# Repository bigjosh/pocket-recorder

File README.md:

# Pocket Recorder Hardware Workspace

Ready-to-iterate KiCad 8/9 hardware workspace for the **Low-Power Outdoor Audio Recorder** (`30.0 x 48.0 mm`, 4-layer 1.6 mm PCBWay Matte-Black ENIG, STM32U595RJT6Q / U5A5 drop-in, TDK T5837 PDM mic, RV-3032-C7 RTC, Hirose DM3D-SF microSD).

## Contents
- `SPEC.md` — Original hardware specification.
- `GEMINI.md` — Persistent agent context (all 13 locked design decisions, hard mechanical constraints, STM32U5 pin-swap guardrails, and Definition of Done) loaded automatically by **Gemini CLI**.
- `build_pocket_recorder.py` — Generates `pocket_recorder_hw/pocket_recorder.kicad_pro`, `pocket_recorder.kicad_pcb`, `pocket_recorder_bom.csv`, and `export_pcbway_gerbers.sh`.
- `build_pocket_recorder_sch.py` — Generates the 1:1 synchronized `pocket_recorder_hw/pocket_recorder.kicad_sch`.
- `verify.py` — Automated gatekeeper script (mechanical assertions, sch<->pcb parity, Freerouting CLI bridge, KiCad ERC/DRC JSON parser, and layer SVG/PNG renders).
- `pocket_recorder_hw/` — Pre-generated KiCad 8/9 project, BOM, and PCBWay Gerber export script.
- `.gemini/settings.json.example` — Optional template for adding `KiCAD-MCP-Server` to Gemini CLI.

## Quick Start with Gemini CLI

1. **Initialize Git** so the agent can checkpoint and revert placement/routing trials safely:
   ```bash
   git init
   git add .
   git commit -m "Initial verified architecture, schematic, and pre-placed 4L PCB"
   ```

2. **Check local tools:**
   ```bash
   kicad-cli --version
   python3 verify.py --mech-only
   ```
   *(Install [Freerouting](https://github.com/freerouting/freerouting/releases) to enable automated routing via `python3 verify.py --route`.)*

3. **Launch Gemini CLI** in this directory:
   ```bash
   gemini
   ```
   Confirm `GEMINI.md` and `SPEC.md` loaded with `/memory show`, then prompt:
   > Review `GEMINI.md` and run `python3 verify.py`. Iteratively refine component placement, safe STM32 pin swaps, critical-net routing (`USB_DP`/`DM` 90R, `L1`/`L2` switch loops, `Y1` HSE, `MK1` PDM), and Freerouting passes until `verify.py` exits 0 with 0 ERC, 0 DRC, and 0 unrouted nets, then export `pocket_recorder_pcbway_gerbers.zip`.

## PCBWay Order Settings (Ready to Fab)
- **Upload Archive:** `pocket_recorder_hw/pocket_recorder_pcbway_gerbers.zip` (full turnkey bundle with BOM, CPL, KiCad sources & 3D renders: `pocket_recorder_hw/pocket_recorder_production_package_v1.0.0.zip`)
- **Size:** `30.0 x 48.0 mm`, `R1.5 mm` corners
- **Layers / Thickness:** 4 Layers, `1.6 mm`, FR-4 TG150-160 (`1 oz` outer / `0.5 oz` inner)
- **Finish:** ENIG (1U" or 2U")
- **Solder Mask:** **Matte Black** (PCBWay Special Options)
- **Silkscreen:** White — **Both Sides** (`F.SilkS` carries minimalist flanking upward arrows, hole rings, and unlock/lock icons; `B.SilkS` carries parts-side legends)
- **Via Process:** Tenting vias (all vias covered by solder mask)
- **Impedance Control:** `90 ohm +/-10%` differential pair (`USB_DP`/`USB_DM`, `19.586 mm`, `0.001 mm` skew, over solid `In1.Cu` GND)
- **Fab Note:** *"Top (`F.Mask`) contains intentional thumbprint graphic openings over copper pour; `F.SilkS` contains intentional white icon artwork. Do NOT add PCBWay order number on Top side—place on Bottom (`B.SilkS`) inside 1.0 mm rim."*

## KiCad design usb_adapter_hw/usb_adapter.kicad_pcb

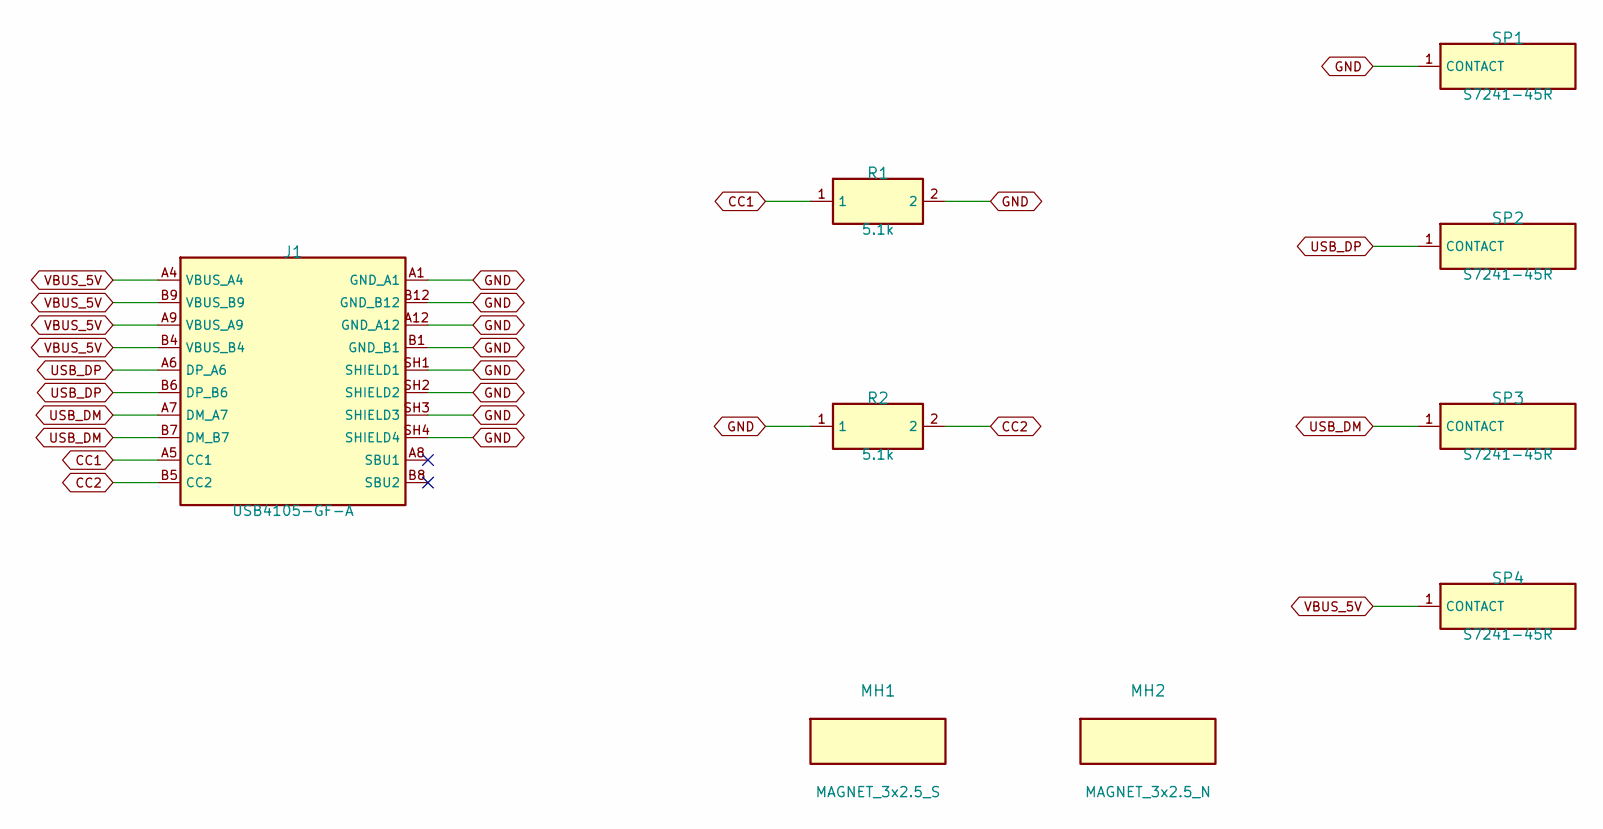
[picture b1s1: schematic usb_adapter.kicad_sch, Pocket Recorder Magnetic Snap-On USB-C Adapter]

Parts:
J1: USB4105-GF-A; USB_C_Receptacle_GCT_USB4105-xx-A_16P_TopMnt_Horizontal; MPN USB4105-GF-A
MH1: MAGNET_3x2.5_S; MagnetHole_3.15mm_NPTH; MPN MAGNET_3x2.5MM_N52
MH2: MAGNET_3x2.5_N; MagnetHole_3.15mm_NPTH; MPN MAGNET_3x2.5MM_N52
R1, R2: 5.1k; R_0603_1608Metric; MPN RC0603FR-075K1L
SP1, SP2, SP3, SP4: S7241-45R; Harwin_S7241-45R_SpringFinger; MPN S7241-45R

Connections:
CC1: J1.A5 (CC1), R1.1
CC2: J1.B5 (CC2), R2.2
GND: J1.A1 (GND_A1), J1.A12 (GND_A12), J1.B1 (GND_B1), J1.B12 (GND_B12), J1.SH1 (SHIELD1), J1.SH2 (SHIELD2), J1.SH3 (SHIELD3), J1.SH4 (SHIELD4), R1.2, R2.1, SP1.1
USB_DM: J1.A7 (DM_A7), J1.B7 (DM_B7), SP3.1
USB_DP: J1.A6 (DP_A6), J1.B6 (DP_B6), SP2.1
VBUS_5V: J1.A4 (VBUS_A4), J1.A9 (VBUS_A9), J1.B4 (VBUS_B4), J1.B9 (VBUS_B9), SP4.1

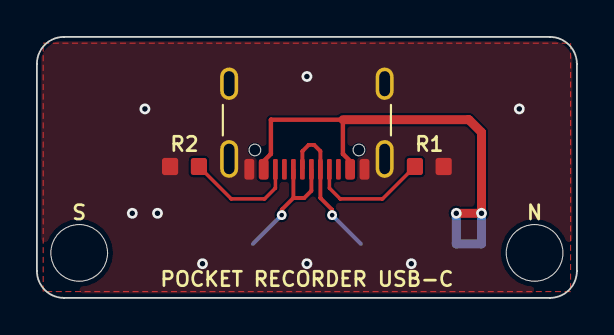
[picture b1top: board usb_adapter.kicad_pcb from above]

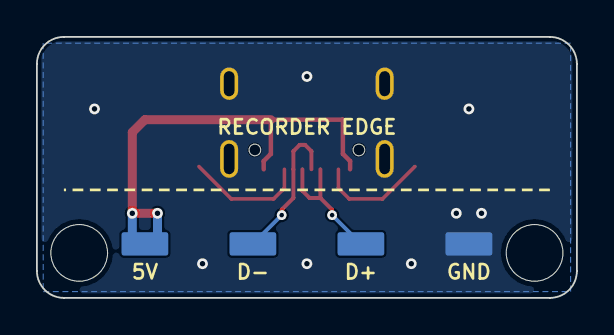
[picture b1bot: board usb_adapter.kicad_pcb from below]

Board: 2 copper layers, 30.0 x 14.5 mm, 9 parts (4 on the bottom side), 6 nets.

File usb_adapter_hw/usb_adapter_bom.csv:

Designator,Qty,MPN,Manufacturer,Package,Description,Order_Link
J1,1,USB4105-GF-A,GCT,USB-C 16P Top-Mount,USB 2.0 Type-C Receptacle (4x THT Shield Legs),https://www.digikey.com/en/products/detail/gct/USB4105-GF-A/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
"R1,R2",2,RC0603FR-075K1L,Yageo,0603,5.1k 1% USB-C UFP CC1/CC2 Pull-Down,https://www.digikey.com/en/products/detail/yageo/RC0603FR-07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
SP1-SP4,4,S7241-45R,Harwin,SMT 3.0x1.5x1.3mm,"Gold SMT Spring Finger (1.0mm working H, ~40gf)",https://www.digikey.com/en/products/detail/harwin-inc/S7241-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

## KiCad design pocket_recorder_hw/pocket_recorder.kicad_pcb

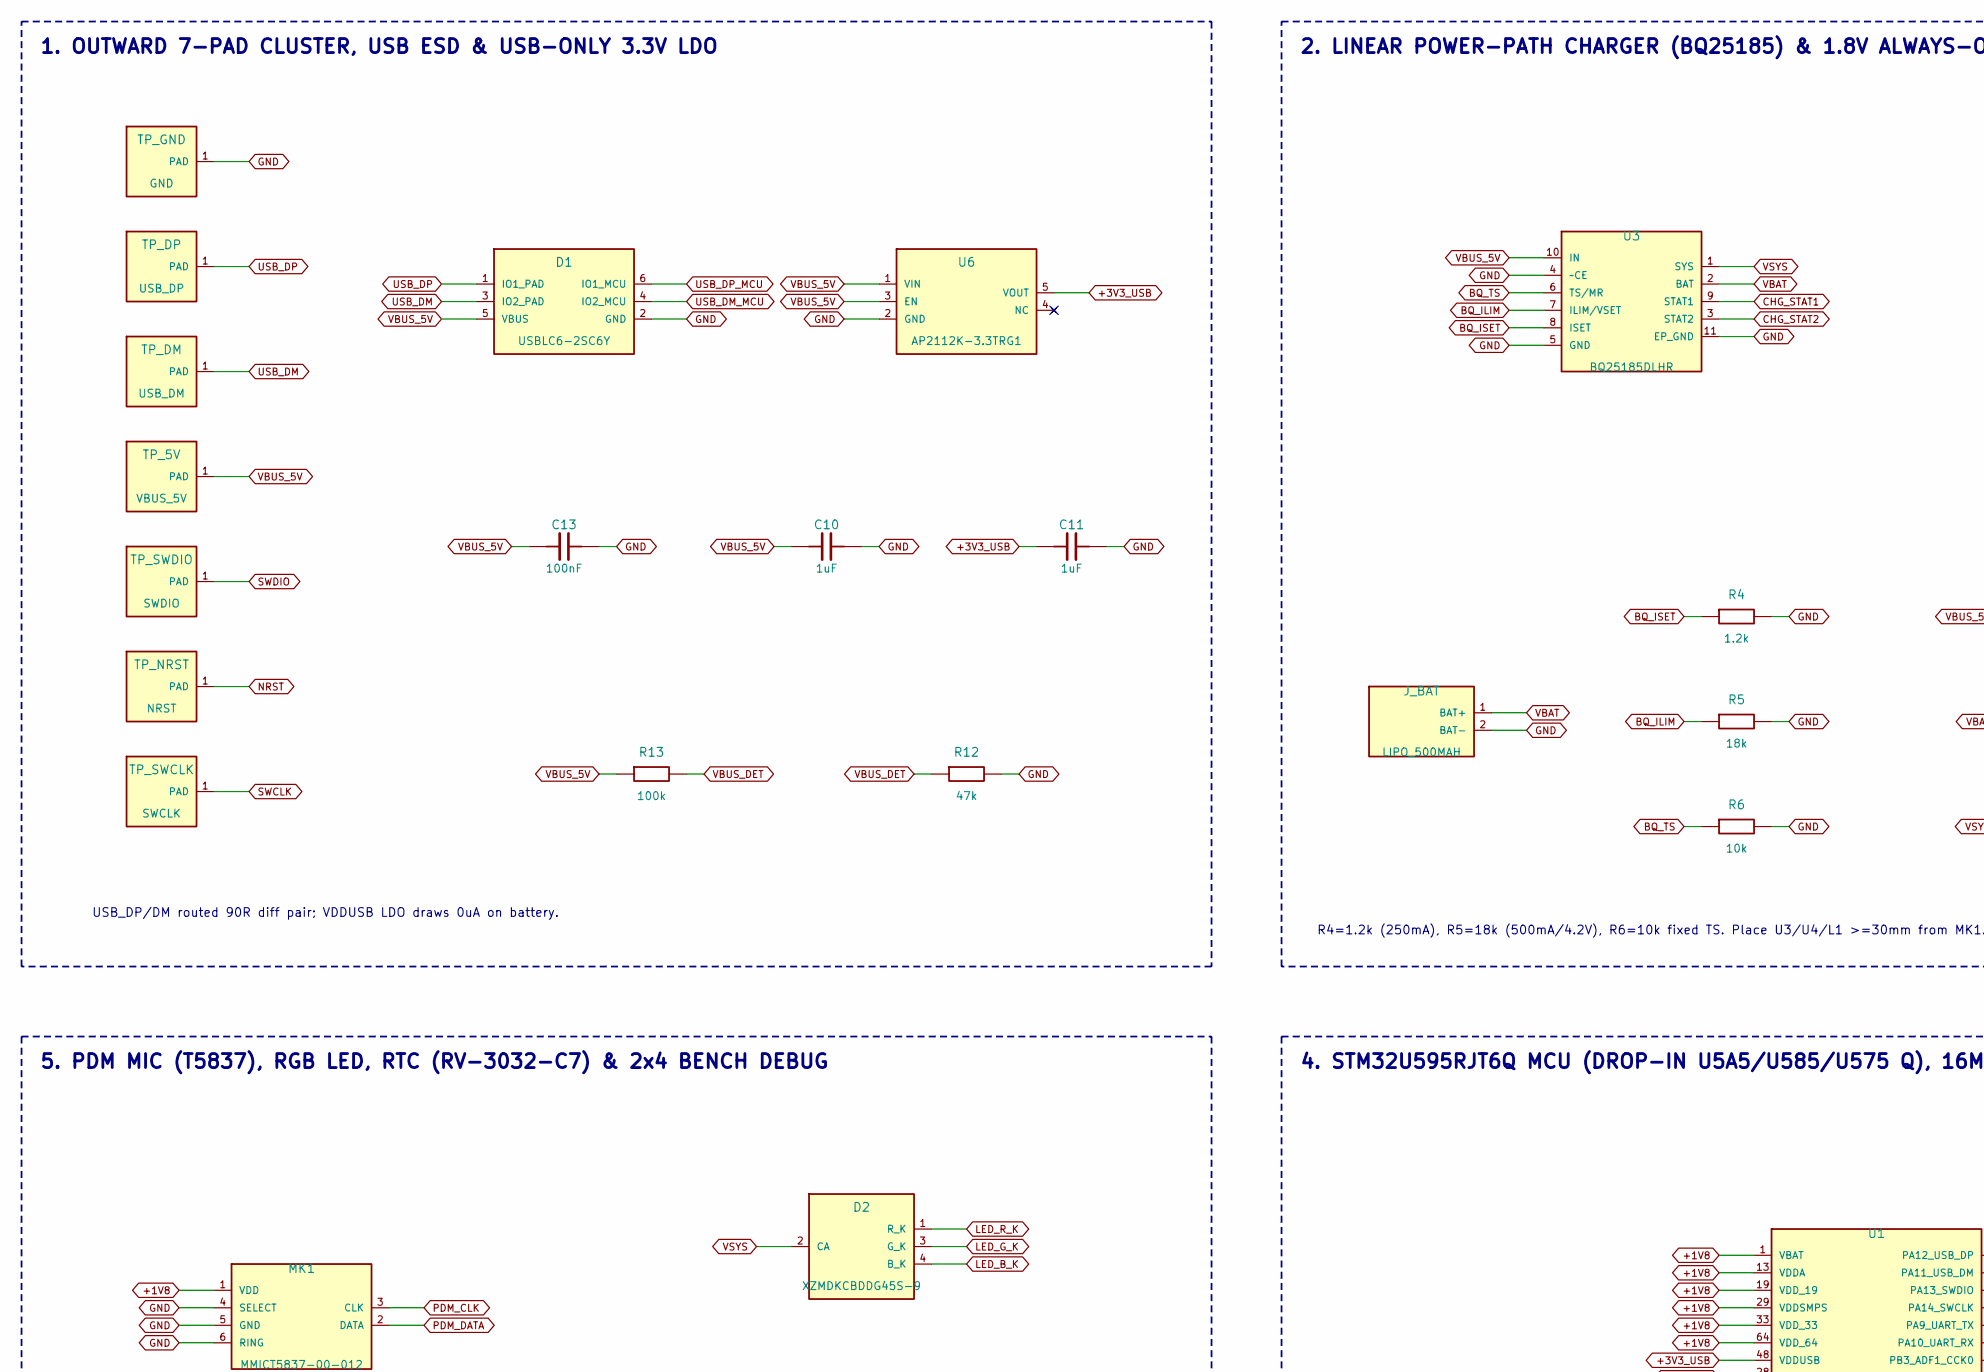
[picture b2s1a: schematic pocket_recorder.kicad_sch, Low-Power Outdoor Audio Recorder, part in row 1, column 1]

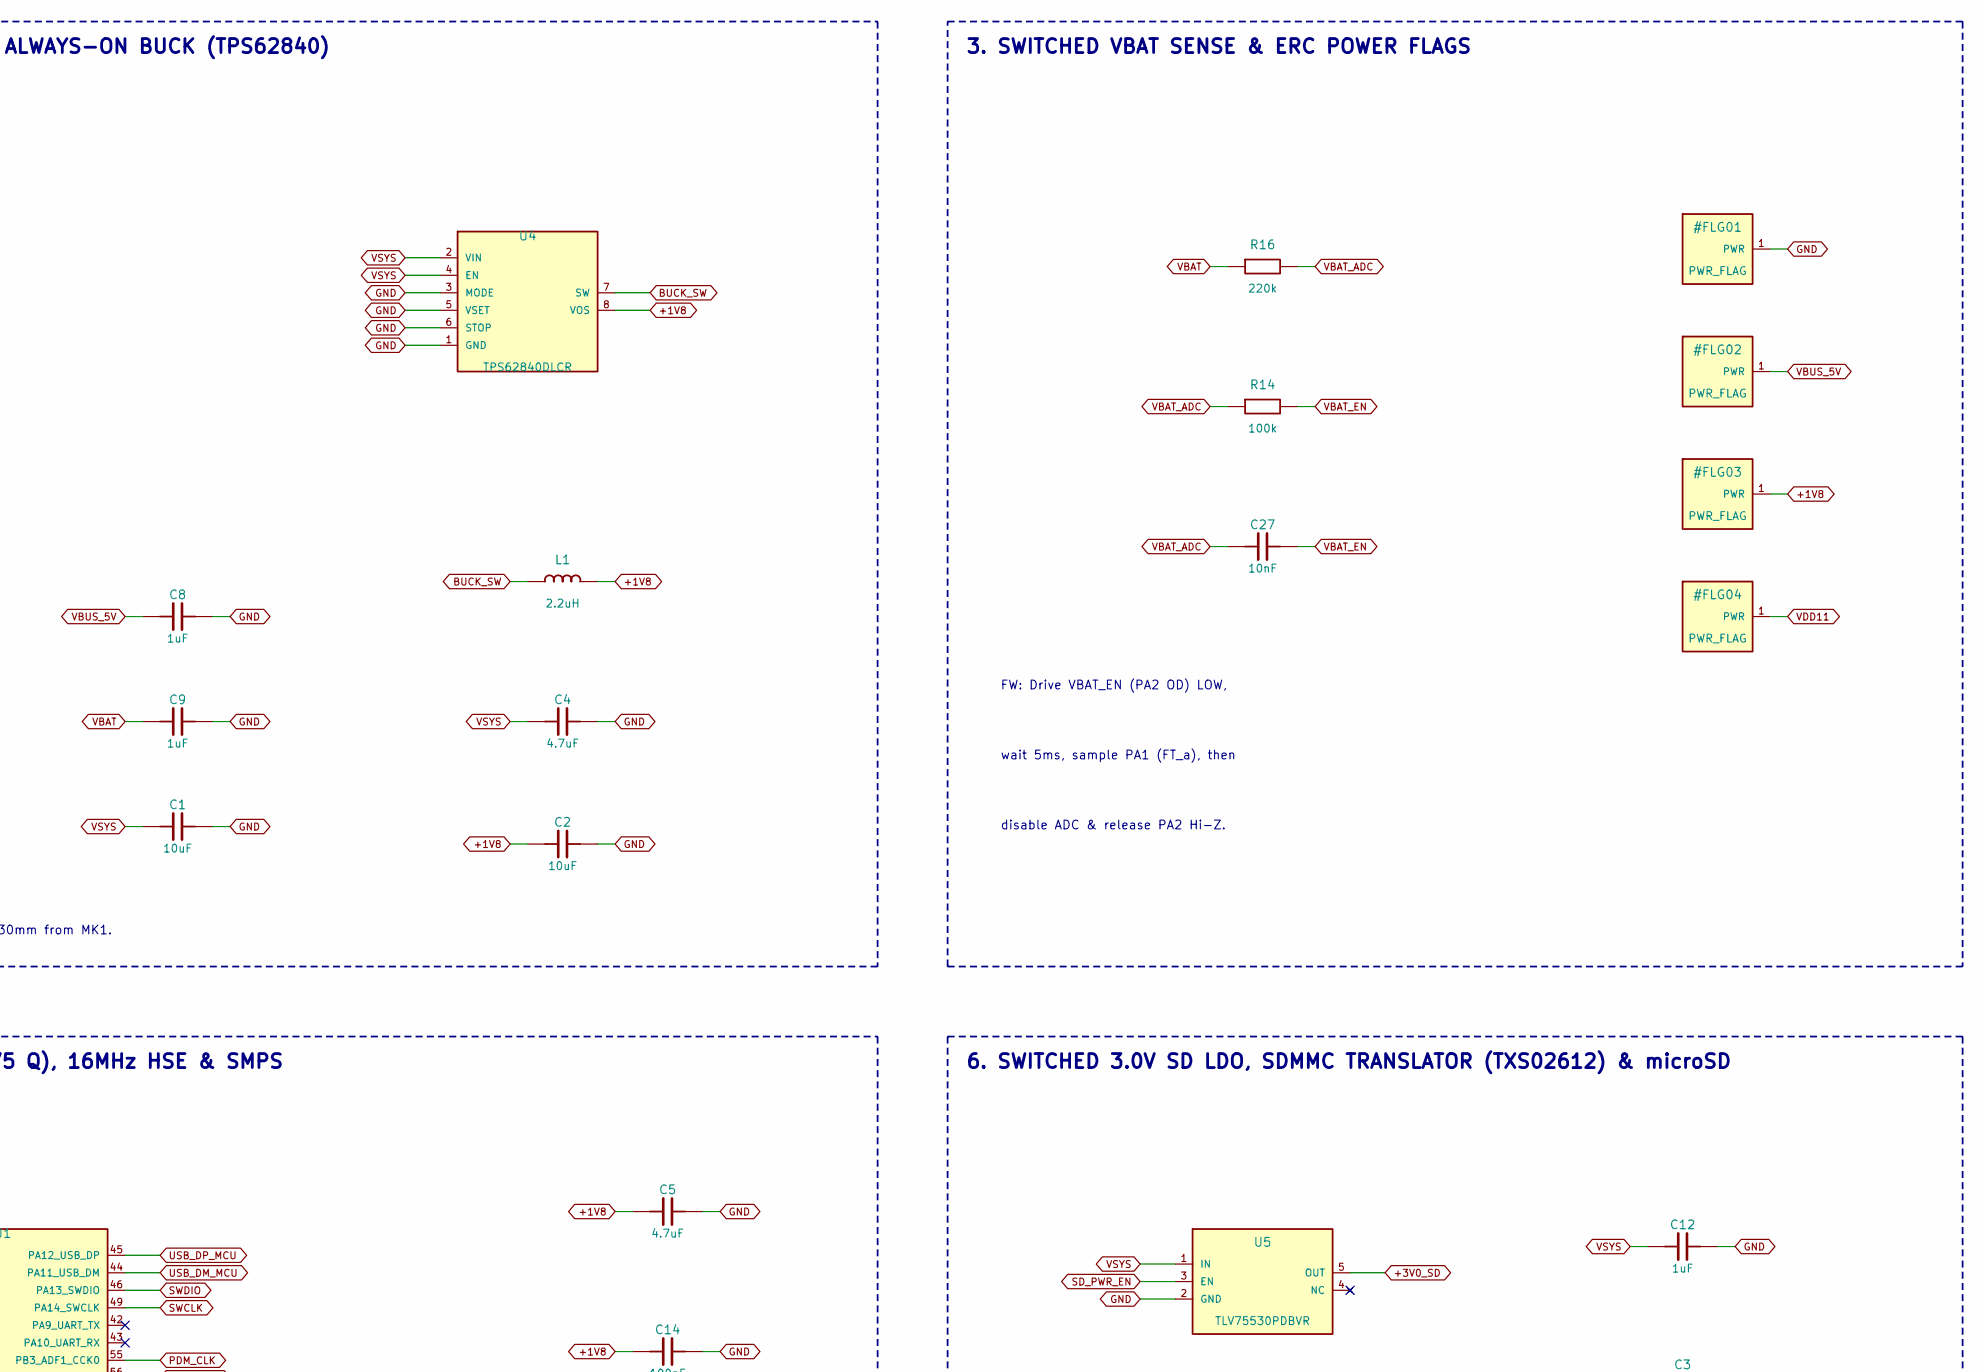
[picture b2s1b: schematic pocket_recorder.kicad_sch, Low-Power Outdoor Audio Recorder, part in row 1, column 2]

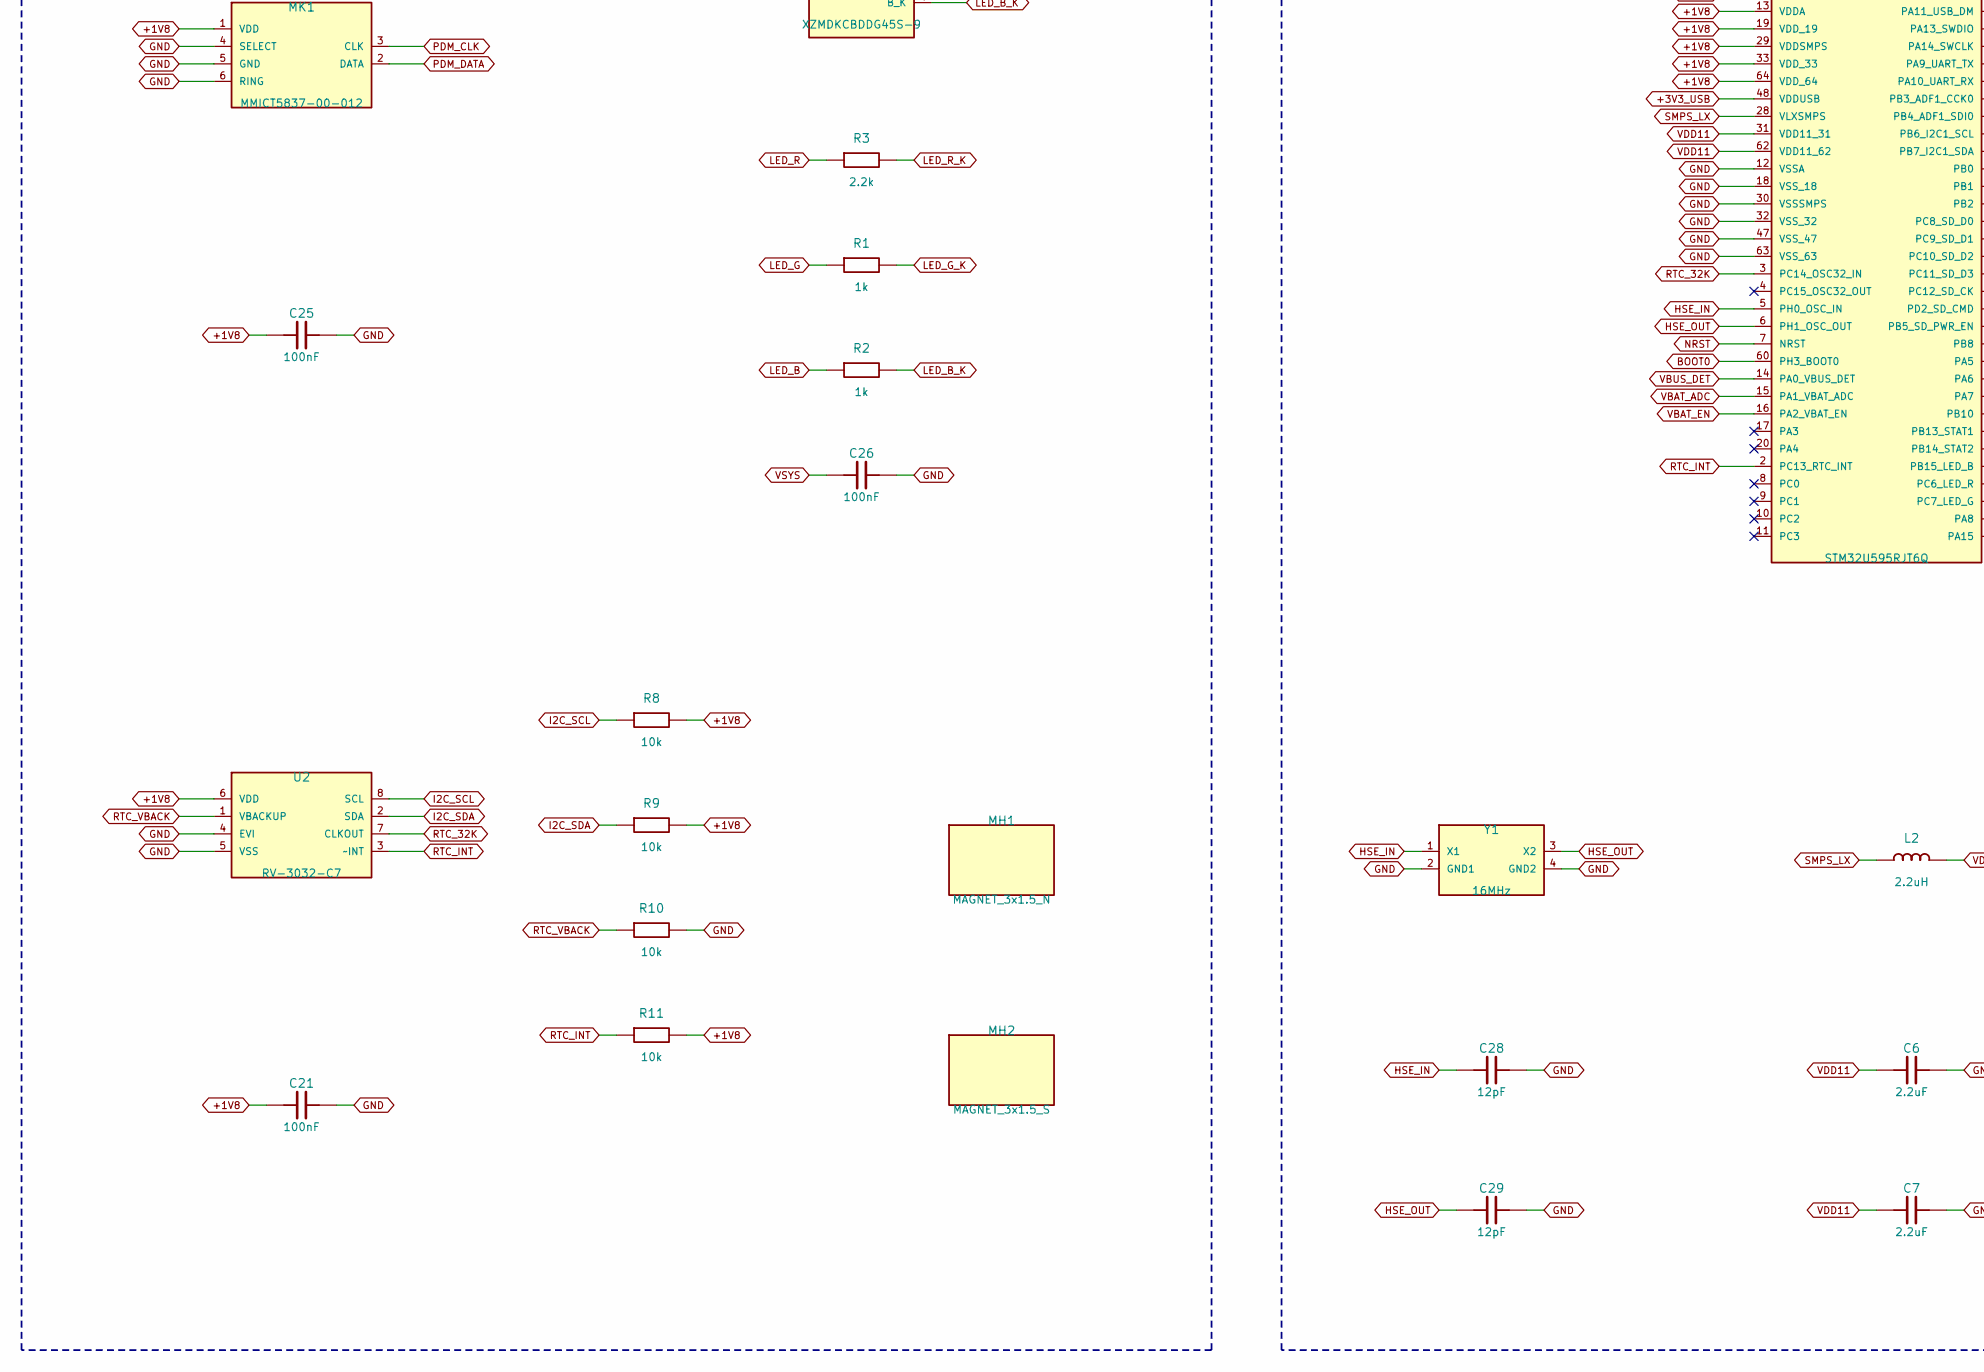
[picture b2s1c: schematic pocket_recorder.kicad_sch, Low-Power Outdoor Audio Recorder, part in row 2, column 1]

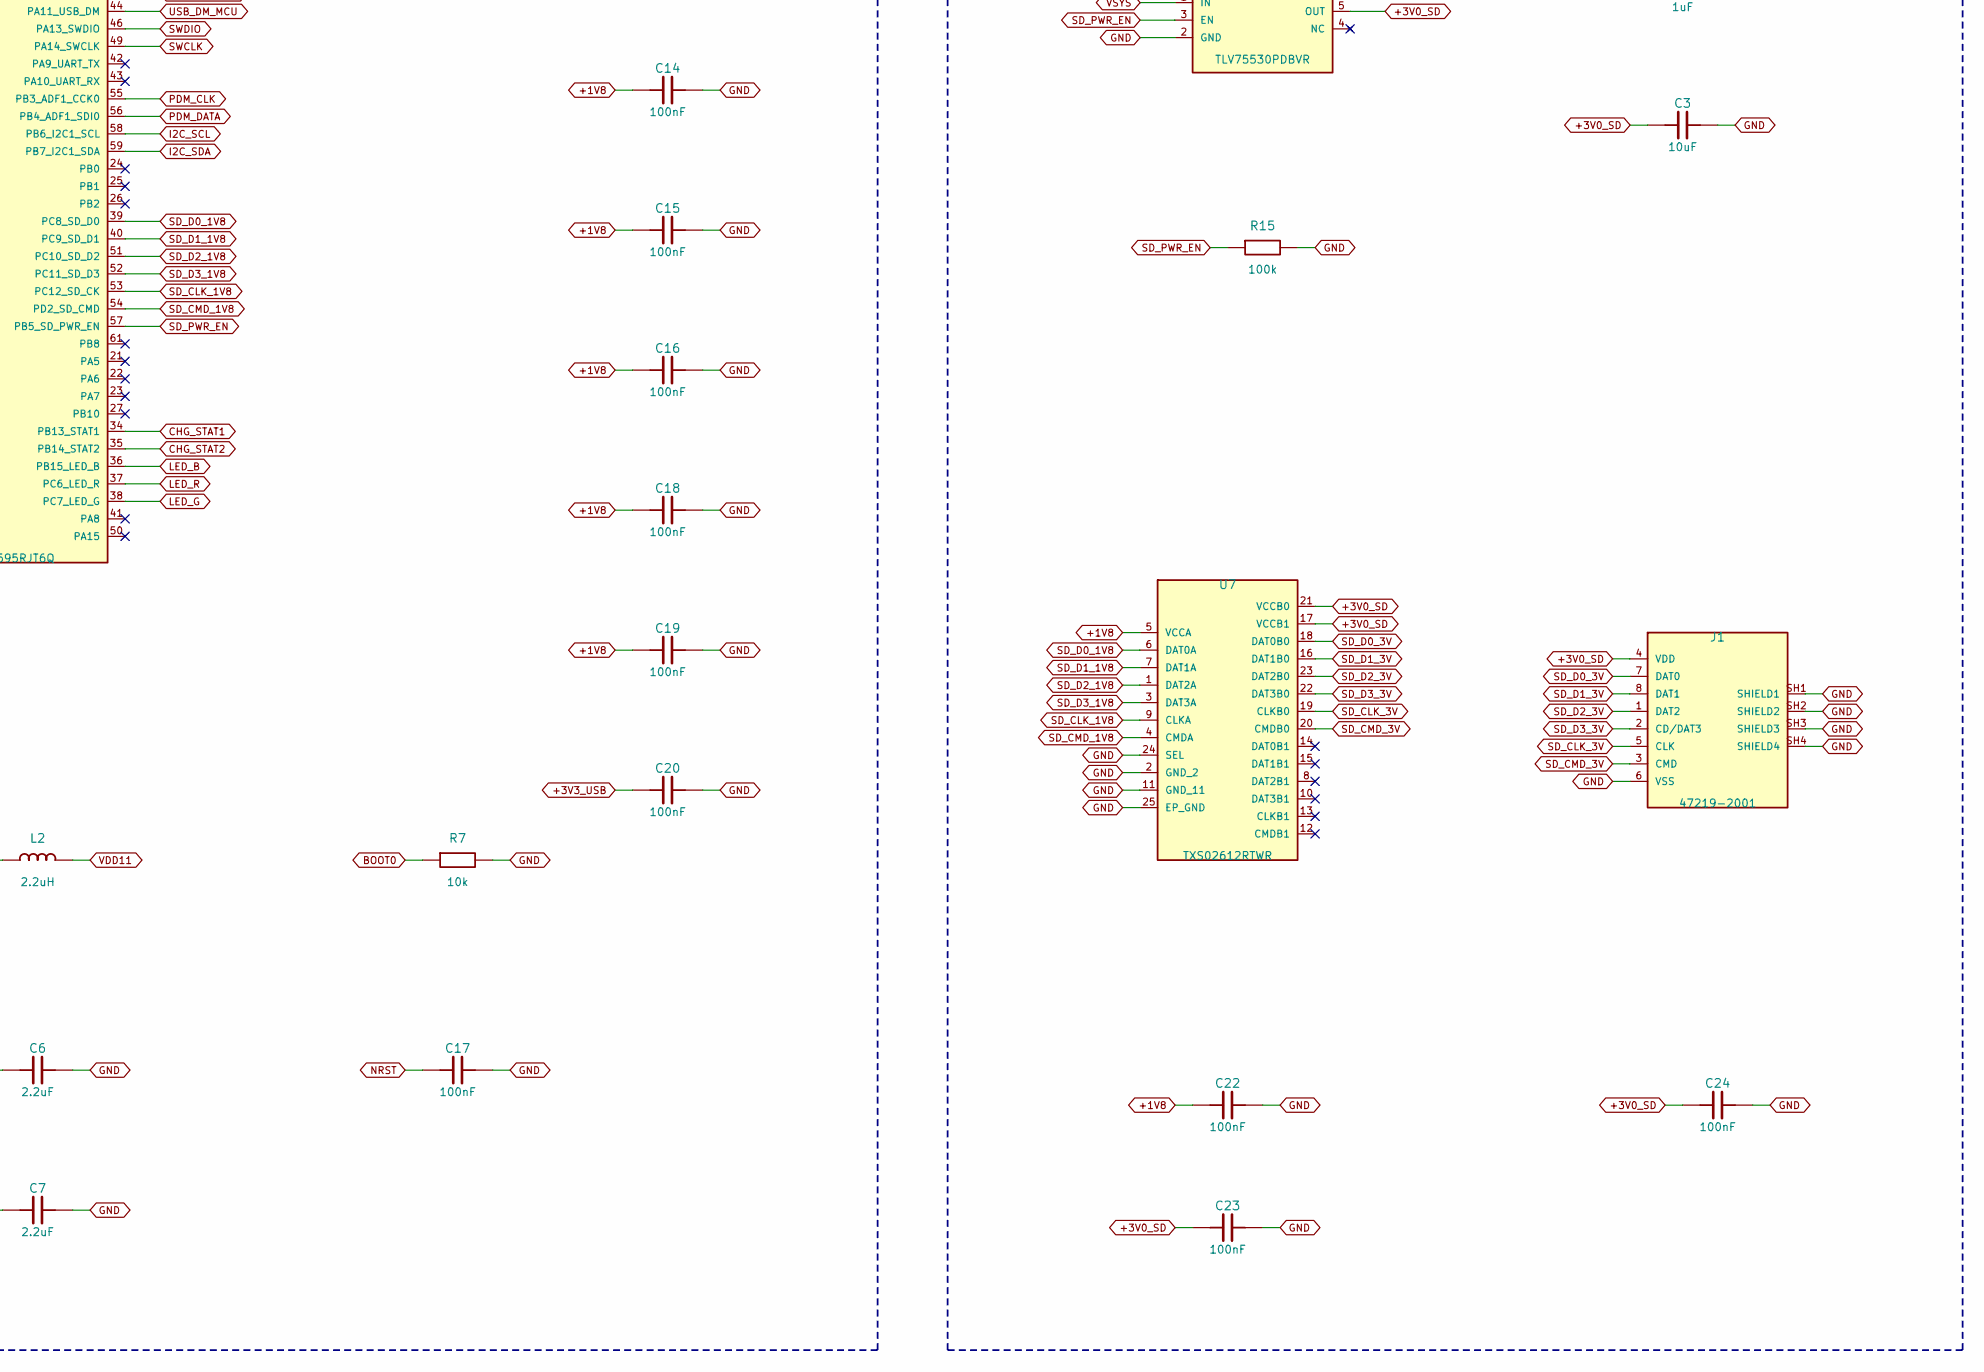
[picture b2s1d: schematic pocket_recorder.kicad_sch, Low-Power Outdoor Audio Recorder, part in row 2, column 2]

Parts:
C1, C2, C3: 10uF; R_0603_1608Metric; MPN CL10A106KP8NNNC
C4, C5: 4.7uF; R_0603_1608Metric; MPN CL10A475KP8NNNC
C6, C7: 2.2uF; R_0603_1608Metric; MPN CL10A225KP8NNNC
C8, C9, C10, C11, C12: 1uF; R_0603_1608Metric; MPN CL10A105KB8NNNC
C13, C14, C15, C16, C17, C18, C19, C20, C21, C22, C23, C24, C25, C26: 100nF; R_0603_1608Metric; MPN CL10B104KB8NNNC
C27: 10nF; R_0603_1608Metric; MPN CL10B103KB8NNNC
C28, C29: 12pF; R_0603_1608Metric; MPN CL10C120JB8NNNC
D1: USBLC6-2SC6Y; SOT-23-6; MPN USBLC6-2SC6Y
D2: XZMDKCBDDG45S-9; SunLED_XZMDKCBDDG45S-9_ReverseMount; MPN XZMDKCBDDG45S-9
J1: 47219-2001; microSD_HC_Molex_47219-2001; MPN 47219-2001
J_BAT: LIPO_500MAH; LiPo_SolderPads_2P; MPN SOLDER_PADS
L1, L2: 2.2uH; L_2016_Murata_DFE201610E; MPN DFE201610E-2R2M=P2
MH1: MAGNET_3x1.5_N; MagnetHole_3.15mm_NPTH; MPN MAGNET_3x1.5MM_N52
MH2: MAGNET_3x1.5_S; MagnetHole_3.15mm_NPTH; MPN MAGNET_3x1.5MM_N52
MK1: MMICT5837-00-012; TDK_T5837_T5838_BottomPort; MPN MMICT5837-00-012
R1, R2: 1k; R_0603_1608Metric; MPN RC0603FR-071KL
R3: 2.2k; R_0603_1608Metric; MPN RC0603FR-072K2L
R4: 1.2k; R_0603_1608Metric; MPN RC0603FR-071K2L
R5: 18k; R_0603_1608Metric; MPN RC0603FR-0718KL
R6, R7, R8, R9, R10, R11: 10k; R_0603_1608Metric; MPN RC0603FR-0710KL
R12: 47k; R_0603_1608Metric; MPN RC0603FR-0747KL
R13, R14, R15: 100k; R_0603_1608Metric; MPN RC0603FR-07100KL
R16: 220k; R_0603_1608Metric; MPN RC0603FR-07220KL
TP_5V: VBUS_5V; PogoPad_3x3mm_ENIG; MPN ENIG_3x3mm
TP_DM: USB_DM; PogoPad_3x3mm_ENIG; MPN ENIG_3x3mm
TP_DP: USB_DP; PogoPad_3x3mm_ENIG; MPN ENIG_3x3mm
TP_GND: GND; PogoPad_3x3mm_ENIG; MPN ENIG_3x3mm
TP_NRST: NRST; PogoPad_3x3mm_ENIG; MPN ENIG_3x3mm
TP_SWCLK: SWCLK; PogoPad_3x3mm_ENIG; MPN ENIG_3x3mm
TP_SWDIO: SWDIO; PogoPad_3x3mm_ENIG; MPN ENIG_3x3mm
U1: STM32U595RJT6Q; LQFP-64_10x10mm_P0.5mm; MPN STM32U595RJT6Q
U2: RV-3032-C7; MicroCrystal_RV-3032-C7; MPN RV-3032-C7-32.768KHZ-2.5PPM-TA-QC
U3: BQ25185DLHR; WSON-10-1EP_2.2x2mm_P0.4mm; MPN BQ25185DLHR
U4: TPS62840DLCR; Texas_VSON-HR-8_1.5x2mm_P0.5mm; MPN TPS62840DLCR
U5: TLV75530PDBVR; SOT-23-5; MPN TLV75530PDBVR
U6: AP2112K-3.3TRG1; SOT-23-5; MPN AP2112K-3.3TRG1
U7: TXS02612RTWR; WQFN-24-1EP_4x4mm_P0.5mm; MPN TXS02612RTWR
Y1: 16MHz; Crystal_SMD_3225-4Pin; MPN CX3225SB16000D0FLJCC

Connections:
+1V8: C2.1, C5.1, C14.1, C15.1, C16.1, C18.1, C19.1, C21.1, C22.1, C25.1, L1.2, MK1.1 (VDD), R8.2, R9.2, R11.2, U1.1 (VBAT), U1.13 (VDDA), U1.19 (VDD_19), U1.29 (VDDSMPS), U1.33 (VDD_33), U1.64 (VDD_64), U2.6 (VDD), U4.8 (VOS), U7.5 (VCCA)
+3V0_SD: C3.1, C23.1, C24.1, J1.4 (VDD), U5.5 (OUT), U7.17 (VCCB1), U7.21 (VCCB0)
+3V3_USB: C11.1, C20.1, U1.48 (VDDUSB), U6.5 (VOUT)
BOOT0: R7.1, U1.60 (PH3_BOOT0)
BQ_ILIM: R5.1, U3.7 (ILIM/VSET)
BQ_ISET: R4.1, U3.8 (ISET)
BQ_TS: R6.1, U3.6 (TS/MR)
BUCK_SW: L1.1, U4.7 (SW)
CHG_STAT1: U1.34 (PB13_STAT1), U3.9 (STAT1)
CHG_STAT2: U1.35 (PB14_STAT2), U3.3 (STAT2)
GND: C1.2, C2.2, C3.2, C4.2, C5.2, C6.2, C7.2, C8.2, C9.2, C10.2, C11.2, C12.2, C13.2, C14.2, C15.2, C16.2, C17.2, C18.2, C19.2, C20.2, C21.2, C22.2, C23.2, C24.2, C25.2, C26.2, C28.2, C29.2, D1.2 (GND), J1.6 (VSS), J1.SH1 (SHIELD1), J1.SH2 (SHIELD2), J1.SH3 (SHIELD3), J1.SH4 (SHIELD4), J_BAT.2 (BAT-), MK1.4 (SELECT), MK1.5 (GND), MK1.6 (RING), R4.2, R5.2, R6.2, R7.2, R10.2, R12.2, R15.2, TP_GND.1, U1.12 (VSSA), U1.18 (VSS_18), U1.30 (VSSSMPS), U1.32 (VSS_32), U1.47 (VSS_47), U1.63 (VSS_63), U2.4 (EVI), U2.5 (VSS), U3.4 (~CE), U3.5 (GND), U3.11 (EP_GND), U4.1 (GND), U4.3 (MODE), U4.5 (VSET), U4.6 (STOP), U5.2 (GND), U6.2 (GND), U7.2 (GND_2), U7.11 (GND_11), U7.24 (SEL), U7.25 (EP_GND), Y1.2 (GND1), Y1.4 (GND2)
HSE_IN: C28.1, U1.5 (PH0_OSC_IN), Y1.1 (X1)
HSE_OUT: C29.1, U1.6 (PH1_OSC_OUT), Y1.3 (X2)
I2C_SCL: R8.1, U1.58 (PB6_I2C1_SCL), U2.8 (SCL)
I2C_SDA: R9.1, U1.59 (PB7_I2C1_SDA), U2.2 (SDA)
LED_B: R2.1, U1.36 (PB15_LED_B)
LED_B_K: D2.4 (B_K), R2.2
LED_G: R1.1, U1.38 (PC7_LED_G)
LED_G_K: D2.3 (G_K), R1.2
LED_R: R3.1, U1.37 (PC6_LED_R)
LED_R_K: D2.1 (R_K), R3.2
NRST: C17.1, TP_NRST.1, U1.7 (NRST)
PDM_CLK: MK1.3 (CLK), U1.55 (PB3_ADF1_CCK0)
PDM_DATA: MK1.2 (DATA), U1.56 (PB4_ADF1_SDI0)
RTC_32K: U1.3 (PC14_OSC32_IN), U2.7 (CLKOUT)
RTC_INT: R11.1, U1.2 (PC13_RTC_INT), U2.3 (~INT)
RTC_VBACK: R10.1, U2.1 (VBACKUP)
SD_CLK_1V8: U1.53 (PC12_SD_CK), U7.9 (CLKA)
SD_CLK_3V: J1.5 (CLK), U7.19 (CLKB0)
SD_CMD_1V8: U1.54 (PD2_SD_CMD), U7.4 (CMDA)
SD_CMD_3V: J1.3 (CMD), U7.20 (CMDB0)
SD_D0_1V8: U1.39 (PC8_SD_D0), U7.6 (DAT0A)
SD_D0_3V: J1.7 (DAT0), U7.18 (DAT0B0)
SD_D1_1V8: U1.40 (PC9_SD_D1), U7.7 (DAT1A)
SD_D1_3V: J1.8 (DAT1), U7.16 (DAT1B0)
SD_D2_1V8: U1.51 (PC10_SD_D2), U7.1 (DAT2A)
SD_D2_3V: J1.1 (DAT2), U7.23 (DAT2B0)
SD_D3_1V8: U1.52 (PC11_SD_D3), U7.3 (DAT3A)
SD_D3_3V: J1.2 (CD/DAT3), U7.22 (DAT3B0)
SD_PWR_EN: R15.1, U1.57 (PB5_SD_PWR_EN), U5.3 (EN)
SMPS_LX: L2.1, U1.28 (VLXSMPS)
SWCLK: TP_SWCLK.1, U1.49 (PA14_SWCLK)
SWDIO: TP_SWDIO.1, U1.46 (PA13_SWDIO)
USB_DM: D1.3 (IO2_PAD), TP_DM.1
USB_DM_MCU: D1.4 (IO2_MCU), U1.44 (PA11_USB_DM)
USB_DP: D1.1 (IO1_PAD), TP_DP.1
USB_DP_MCU: D1.6 (IO1_MCU), U1.45 (PA12_USB_DP)
VBAT: C9.1, J_BAT.1 (BAT+), R16.1, U3.2 (BAT)
VBAT_ADC: C27.1, R14.1, R16.2, U1.15 (PA1_VBAT_ADC)
VBAT_EN: C27.2, R14.2, U1.16 (PA2_VBAT_EN)
VBUS_5V: C8.1, C10.1, C13.1, D1.5 (VBUS), R13.1, TP_5V.1, U3.10 (IN), U6.1 (VIN), U6.3 (EN)
VBUS_DET: R12.1, R13.2, U1.14 (PA0_VBUS_DET)
VDD11: C6.1, C7.1, L2.2, U1.31 (VDD11_31), U1.62 (VDD11_62)
VSYS: C1.1, C4.1, C12.1, C26.1, D2.2 (CA), U3.1 (SYS), U4.2 (VIN), U4.4 (EN), U5.1 (IN)

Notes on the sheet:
1. OUTWARD 7-PAD CLUSTER, USB ESD & USB-ONLY 3.3V LDO
USB_DP/DM routed 90R diff pair; VDDUSB LDO draws 0uA on battery.
2. LINEAR POWER-PATH CHARGER (BQ25185) & 1.8V ALWAYS-ON BUCK (TPS62840)
R4=1.2k (250mA), R5=18k (500mA/4.2V), R6=10k fixed TS. Place U3/U4/L1 >=30mm from MK1.
3. SWITCHED VBAT SENSE & ERC POWER FLAGS
FW: Drive VBAT_EN (PA2 OD) LOW,
wait 5ms, sample PA1 (FT_a), then
disable ADC & release PA2 Hi-Z.
4. STM32U595RJT6Q MCU (DROP-IN U5A5/U585/U575 Q), 16MHz HSE & SMPS
5. PDM MIC (T5837), RGB LED, RTC (RV-3032-C7) & 2x4 BENCH DEBUG
6. SWITCHED 3.0V SD LDO, SDMMC TRANSLATOR (TXS02612) & microSD

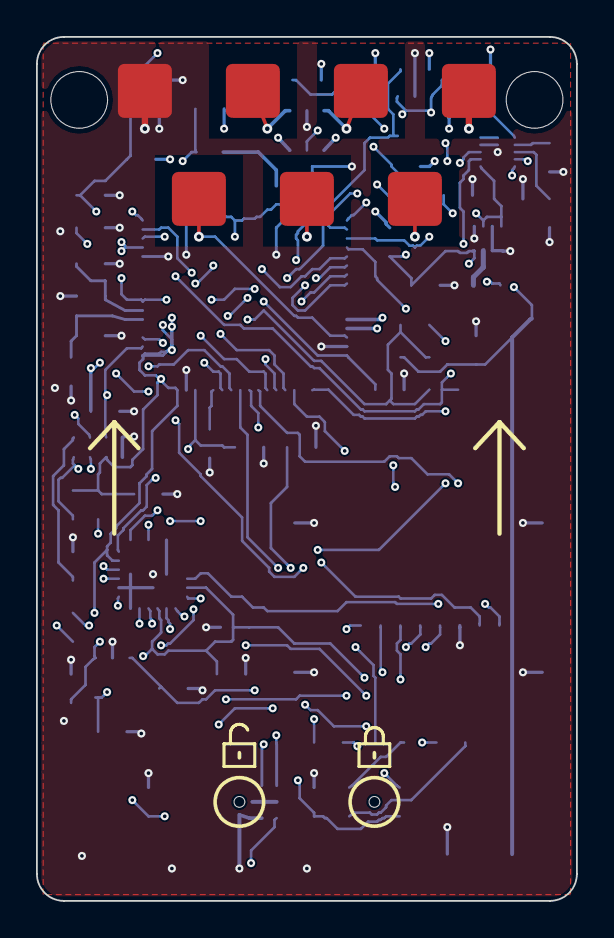
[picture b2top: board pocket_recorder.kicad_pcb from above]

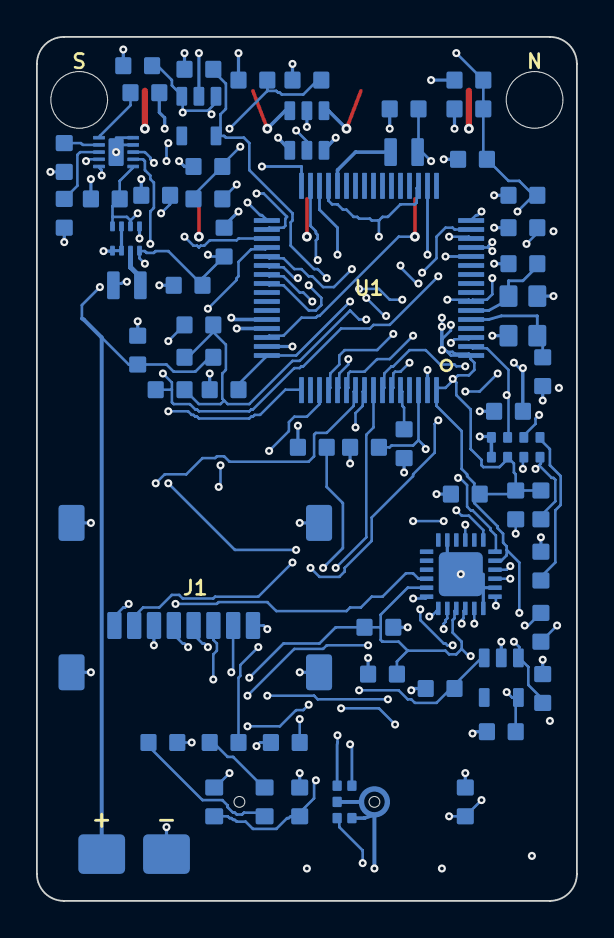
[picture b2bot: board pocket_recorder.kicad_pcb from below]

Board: 4 copper layers, 30.0 x 48.0 mm, 69 parts (62 on the bottom side), 54 nets.

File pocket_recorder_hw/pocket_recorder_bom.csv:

Designator,Qty,MPN,Manufacturer,Package,Description,Order_Link
U1,1,STM32U595RJT6Q,STMicroelectronics,LQFP64,MCU 4MB USB-HS SMPS (drop-in for U5A5/U585/U575 Q),https://www.mouser.com/en/ProductDetail/STMicroelectronics/S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
MK1,1,MMICT5837-00-012,TDK InvenSense,LGA-6 Bottom Port,PDM MEMS Mic T5837 (fits T5838),https://www.digikey.com/en/products/detail/tdk-invensense/MM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
U2,1,RV-3032-C7-32.768KHZ-2.5PPM-TA-QC,Micro Crystal,SON-8,RTC +/-2.5ppm 32.768kHz CLKOUT,https://www.digikey.com/en/products/detail/micro-crystal-ag/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
U3,1,BQ25185DLHR,Texas Instruments,WSON-10,Linear Power-Path Charger 250mA,https://www.digikey.com/en/products/detail/texas-instruments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
U4,1,TPS62840DLCR,Texas Instruments,VSON-HR-8,1.8V Always-On Buck 60nA Iq,https://www.digikey.com/en/products/detail/texas-instruments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
U5,1,TLV75530PDBVR,Texas Instruments,SOT-23-5,Switched 3.0V 500mA SD LDO,https://www.digikey.com/en/products/detail/texas-instruments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
U6,1,AP2112K-3.3TRG1,Diodes Inc.,SOT-23-5,USB-Only 3.3V LDO for VDDUSB,https://www.digikey.com/en/products/detail/diodes-incorporat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
U7,1,TXS02612RTWR,Texas Instruments,WQFN-24,4-Bit SDMMC Level Translator (Ioff),https://www.digikey.com/en/products/detail/texas-instruments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
D1,1,USBLC6-2SC6Y,STMicroelectronics,SOT-23-6,USB 2.0 HS ESD Protection,https://www.digikey.com/en/products/detail/stmicroelectronic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
D2,1,XZMDKCBDDG45S-9,SunLED,4-PLCC Bottom,Reverse-Mount RGB LED,https://www.digikey.com/en/products/detail/sunled/XZMDKCBDDG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
J1,1,47219-2001,Molex,SMT 1.90mm H,Hinged Clamshell microSD Socket,https://www.digikey.com/en/products/detail/molex/0472192001/1997321
Y1,1,CX3225SB16000D0FLJCC,Kyocera AVX,SMD 3225,16MHz +/-10ppm 8pF HSE Crystal,https://www.digikey.com/en/products/detail/kyocera-avx/CX322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
"L1,L2",2,DFE201610E-2R2M=P2,Murata,2016 1.0mm H,2.2uH Shielded Inductor,https://www.digikey.com/en/products/detail/murata-electronic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
"R1,R2",2,RC0603FR-071KL,Yageo,0603,1k 1% (LED G/B),https://www.digikey.com/en/products/detail/yageo/RC0603FR-07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
R3,1,RC0603FR-072K2L,Yageo,0603,2.2k 1% (LED R),https://www.digikey.com/en/products/detail/yageo/RC0603FR-07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
R4,1,RC0603FR-071K2L,Yageo,0603,1.2k 1% (BQ25185 ISET 250mA),https://www.digikey.com/en/products/detail/yageo/RC0603FR-07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
R5,1,RC0603FR-0718KL,Yageo,0603,18k 1% (BQ25185 ILIM/VSET),https://www.digikey.com/en/products/detail/yageo/RC0603FR-07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
R6-R11,6,RC0603FR-0710KL,Yageo,0603,"10k 1% (TS, BOOT0, I2C, RTC)",https://www.digikey.com/en/products/detail/yageo/RC0603FR-07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
R12,1,RC0603FR-0747KL,Yageo,0603,47k 1% (VBUS_DET bot),https://www.digikey.com/en/products/detail/yageo/RC0603FR-07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
R13-R15,3,RC0603FR-07100KL,Yageo,0603,"100k 1% (VBUS top, VBAT bot, SD_EN PD)",https://www.digikey.com/en/products/detail/yageo/RC0603FR-07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
R16,1,RC0603FR-07220KL,Yageo,0603,220k 1% (VBAT sense top),https://www.digikey.com/en/products/detail/yageo/RC0603FR-07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
C1-C3,3,CL10A106KP8NNNC,Samsung,0603,10uF 10V X5R,https://www.digikey.com/en/products/detail/samsung-electro-m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
"C4,C5",2,CL10A475KP8NNNC,Samsung,0603,4.7uF 10V X5R,https://www.digikey.com/en/products/detail/samsung-electro-m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
"C6,C7",2,CL10A225KP8NNNC,Samsung,0603,2.2uF 10V X5R (VDD11),https://www.digikey.com/en/products/detail/samsung-electro-m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
C8-C12,5,CL10A105KB8NNNC,Samsung,0603,1uF 50V X5R,https://www.digikey.com/en/products/detail/samsung-electro-m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
C13-C26,14,CL10B104KB8NNNC,Samsung,0603,100nF 50V X7R,https://www.digikey.com/en/products/detail/samsung-electro-m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
C27,1,CL10B103KB8NNNC,Samsung,0603,10nF 50V X7R (VBAT ADC),https://www.digikey.com/en/products/detail/samsung-electro-m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
"C28,C29",2,CL10C120JB8NNNC,Samsung,0603,12pF 50V C0G (16MHz HSE),https://www.digikey.com/en/products/detail/samsung-electro-m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

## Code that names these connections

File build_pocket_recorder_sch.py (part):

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    place_part("R_0603", "R16", "220k", "Resistor_SMD:R_0603_1608Metric", "RC0603FR-07220KL", 184, 20, {"1": "VBAT", "2": "VBAT_ADC"}, stub_u=1)
    place_part("R_0603", "R14", "100k", "Resistor_SMD:R_0603_1608Metric", "RC0603FR-07100KL", 184, 28, {"1": "VBAT_ADC", "2": "VBAT_EN"}, stub_u=1)
    place_part("C_0603", "C27", "10nF", "Resistor_SMD:R_0603_1608Metric", "CL10B103KB8NNNC",  184, 36, {"1": "VBAT_ADC", "2": "VBAT_EN"}, stub_u=1)
    add_note("FW: Drive VBAT_EN (PA2 OD) LOW,", 169, 44)
    add_note("wait 5ms, sample PA1 (FT_a), then", 169, 48)
    add_note("disable ADC & release PA2 Hi-Z.", 169, 52)

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        "STM32U595RJT6Q", "U1", "STM32U595RJT6Q",
        "Package_QFP:LQFP-64_10x10mm_P0.5mm", "STM32U595RJT6Q", 112, 92, stm32_nets, stub_u=2,
    )
    place_part("XTAL_4P", "Y1", "16MHz", "Crystal:Crystal_SMD_3225-4Pin", "CX3225SB16000D0FLJCC", 90, 126, {"1": "HSE_IN", "2": "GND", "3": "HSE_OUT", "4": "GND"}, stub_u=1)
    place_part("C_0603", "C28", "12pF", "Resistor_SMD:R_0603_1608Metric", "CL10C120JB8NNNC", 90, 138, {"1": "HSE_IN",  "2": "GND"}, stub_u=1)
    place_part("C_0603", "C29", "12pF", "Resistor_SMD:R_0603_1608Metric", "CL10C120JB8NNNC", 90, 146, {"1": "HSE_OUT", "2": "GND"}, stub_u=1)

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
